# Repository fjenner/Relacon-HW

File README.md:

# Relacon Relay Controller

## Overview

The Relacon relay controller is intended to be an open source hardware alternative to the [ADU218](https://www.ontrak.net/ADU218.htm) USB relay I/O interface from [OnTrak Control Systems, Inc](https://www.ontrak.net). The Relacon is not as robust as the commercial offering, but what it lacks in polish it makes up for in cost. Relacon relay controller is about an order of magnitude cheaper to make yourself compared to purchasing an ADU218.

## License

This hardware is Open Source Hardware licensed under the [Creative Commons Attribution 4.0 International (CC BY 4.0)](https://creativecommons.org/licenses/by/4.0/)  license.

## Features

The Relacon has numerous features that make it attractive for low cost applications:

* 8 solid-state relays capable of switching loads up to 60V AC/DC at 1A
* LED indicators corresponding to each relay output
* 8 digital inputs featuring event counters and configurable debounce setting
* Configurable watchdog to fail-open the relays if not actively receiving data from the host
* Full-speed USB Human Interface Device (HID) interface to PC requiring no custom drivers
* Compatibile with existing ADU218-based software applications
* Open source hardware design
    * Easy to modify to substitute in higher-power relays, etc.
* Open source firmware
    * Potential to utilize additional microcontroller peripherals (or repurpose digital inputs) on the expansion header
* No programmer hardware necessary to load the firmware (uses USB DFU bootloader)

That said, the current version of the Relacon hardware (rev. 1) lacks several of the niceties offered by the commercial ADU218 hardware, as indicated in the table below.

Feature | ADU218 | Relacon
--------|--------|---------
120V load capability | :heavy_check_mark: | :x:<br/>(60V load rating)
24V tolerant inputs | :heavy_check_mark: | :x:<br/>(3.3V inputs)
Operational status LED indicator | :heavy_check_mark: | :x:
Certified to various electrical standards | :heavy_check_mark: | :x:
Sturdy enclosure | :heavy_check_mark: | :x:

### Feature/Pin Mapping

The Relacon hardware follows the protocol and conventions of the OnTrak ADU218 relay controller. Because of hardware differences between the two devices, the port/pin designations used in the protocol layer do not directly map to those of the STM32F042K6. The mappings are shown below:

ADU Protocol Pin/Feature | STM32F042K6 Pin Mapping
-------------------|------------------------------
Relay PORTK[0] | PA0
Relay PORTK[1] | PA1
Relay PORTK[2] | PA2
Relay PORTK[3] | PA3
Relay PORTK[4] | PA4
Relay PORTK[5] | PA5
Relay PORTK[6] | PA6
Relay PORTK[7] | PA7
Digital Input PORTA[0] / Event Counter 0 | PB0
Digital Input PORTA[1] / Event Counter 1 | PB1
Digital Input PORTA[2] / Event Counter 2 | PA8 (note that there is no PB2 pin on the STM32F042K6T6 device)
Digital Input PORTA[3] / Event Counter 3 | PB3
Digital Input PORTB[0] / Event Counter 4 | PB4
Digital Input PORTB[1] / Event Counter 5 | PB5
Digital Input PORTB[2] / Event Counter 6 | PB6
Digital Input PORTB[3] / Event Counter 7 | PB7

Note that the silkscreen labels on the board near the terminal block shows the "K" designation for the relays. The silkscreen on the expansion header shows the actual STM32F042K6 pin names.

## Design

### Design Tools

This hardware was designed using the [KiCad](https://kicad.org/) electronic design automation suite for schematic capture and PCB layout. Additional scripts were used for generating the BOM for assembly [per instructions at JLCPCB](https://support.jlcpcb.com/article/84-how-to-generate-the-bom-and-centroid-file-from-kicad).

### Hardware Design

One of the design goals for this board was to support USB bootloading of the firmware on an unprogrammed microcontroller, allowing anyone to build and program the board without requiring any additional programming hardware. This contrained the selection of microcontrollers quite a bit. Another constraining factor was that I intended from the start to use JLCPCB for the PCB fabrication and assembly, so I was limited to their selection of microcontrollers. I ultimately settled on using a STM32F042K6T6 microcontroller.

Is a 32-bit ARM Cortex-M0 overkill for a simple relay controller? Absolutely. However, it was surprisingly inexpensive (I originally got them for $1.28 in individual quantities, although I may have capitalized on a price mistake, as they're now listed at $3.69 at the time of this writing), has an open source basic peripheral library, is compatible with the open source TinyUSB stack, and allows for the use of the well-known ARM GCC toolchain for firmware development.

The circuit design for this hardware is very straightforward. Power and communication with the PC come from the USB connection. A linear voltage regulator and some filtering capacitors are used to drop the voltage from the 5V USB VBUS power to the 3.3V suitable for the microcontroller. The microcontroller contains the firmware that controls the overall behavior of the product.

Although the STM32F042K6 GPIO pins are capable of sourcing or sinking up to 25mA each, the datasheet specifies that there is a cumulative limit of 80mA sourced or sunk among all GPIO pins. This means that when all 8 relays are enabled, those pins must not source/sink more than 10mA each. While 10mA should be sufficient to drive both the indicator LED and the solid-state relay for that channel, it is only by a narrow margin. In order to get more headroom (which may be useful particularly if additional GPIO are being used on the expansion header), a ULN2803A Darlington transistor array is used to drive the indicator LED and relay. The ULN2803A only draws about 1mA per channel, but can drive up to 500mA per channel. While overkill for the base design, this additional drive strength may be useful for modifications that substitute in traditional electromechanical relays, which typically require much more drive current than solid state relays but also provide higher power load switching.

An expansion header exposing additional pins from the microcontroller has been added for two purposes:
* This exposes the 8 input pins required for maintaining functional equivalence with the ADU218
* This makes additional microcontroller pins available for auxiliary functions through modifications to the open source [firmware](https://github.com/fjenner/Relacon-FW).

## Production

These boards (in particular, the component selection) were designed with [JLCPCB](https://jlcpcb.com/) in mind for low cost manufacturing and assembly. The Gerber files for the relevant layers, as well as the drill files, are located in the [gerber](production/gerber) directory, and have been generated per the instructions from JLCPCB [here](https://support.jlcpcb.com/article/102-kicad-515---generating-gerber-and-drill-files).

The BOM used for the assembly, as well as the pick-and-place files, are located in the [assembly](production/assembly) directory. These files have been prepared as described by [JLCPCB](https://support.jlcpcb.com/article/84-how-to-generate-the-bom-and-centroid-file-from-kicad). JLCPCB has a preview tool that shows the component placement and orientation given the pick-and-place files, and notes that the rotation/orientation [may need to be compensated for](https://support.jlcpcb.com/article/99-does-the-red-dot-means-pin-1-in-the-placement-previewer) if there are discrepancies between the zero-degree orientation of the footprint in the KiCad component library vs. their pick-and-place data for the component. This was the case for the U1, U2, and U3 components, so their rotation was manually adjusted in the pick-and-place files after the initial generation.

### Cost

At the time that I placed my order, the total cost (including shipping) for having JLCPCB fab and assemble 5 boards was $77.67, which comes out to about $15.54 per board. However, this includes a $7 discount from a new user coupon code, and that I believe there may have been a price mistake on the STM32F042K6, so take this cost figure with a grain of salt.

Importantly, JLCPCB does not do any through-hole assembly, so the price above does not include the cost of the through-hole parts: the USB connector, terminal blocks, and pin header. Fortunately, these are relatively low cost components. As of the time of this writing, the total cost to purchase those additional through-hole components for the 5 boards would come out to $8.18 (not including shipping), bringing the cost per board up to $17.18.

## Known Issues

Known issues are tracked in the GitHub issue tracker. However, critical issues affecting fundamental operation of the device are described here.

### BOOT0 Pin is Floating

In the current version of the hardware (Relacon Rev 1), the STM32F042K6 `BOOT0` pin (a.k.a `PB8`) is floating. This means that when the device is connected to USB and powers up, it is indeterminate as to whether it will enter the DFU bootloader or the normal firmware application. While an unfortunate oversight, there are several very easy workarounds for this as described below.

#### Workaround 1: Use a jumper on the expansion header to select the desired boot mode
Using a jumper wire, connect the `PB8` pin on the expansion header to either of the `GND` pins for normal firmware boot, or to the `+3V3` pin for DFU bootloading. Fortunately, because the `PB8` pin is adjacent to a `GND` pin on the header, a standard 2-pin jumper block can be used to pull down the `PB8` pin for normal firmware operation.

#### Workaround 2: Solder a pulldown resistor to the underside of the pin header
A small surface-mount resistor (in the 10k~100k range) can be easily added to the underside of the board, fitting quite nicely between the `PB8` pin and the and the adjacent `GND` pin on the expansion header. This approach is functionally similar to the above except that the expansion header pins are physically freed up during normal operation. You will still need to use a wire to temporarily jump the `PB8` pin to `+3V3` when flashing the firmware with the DFU bootloader.

#### Workaround 3: Disable DFU in the STM32F042K6 option byte after programming
This approach hasn't been tested, but in theory, programming the `BOOT_SEL` bit to 0 and the `nBOOT0` bit to 1 in the STM32F042K6 "option byte" should disable selection of the boot mode through the `BOOT0` pin and cause the device to only boot the user firmware application. This has the disadvantage that it will not be possible to update the firmware (or change the option byte to re-enable the `BOOT0` selection) without additional programming hardware.

## Firmware

For more information about the firmware that runs on the Relacon board, including how to fetch, build, and flash it, see the [Relacon Firmware repository](https://github.com/fjenner/Relacon-FW).

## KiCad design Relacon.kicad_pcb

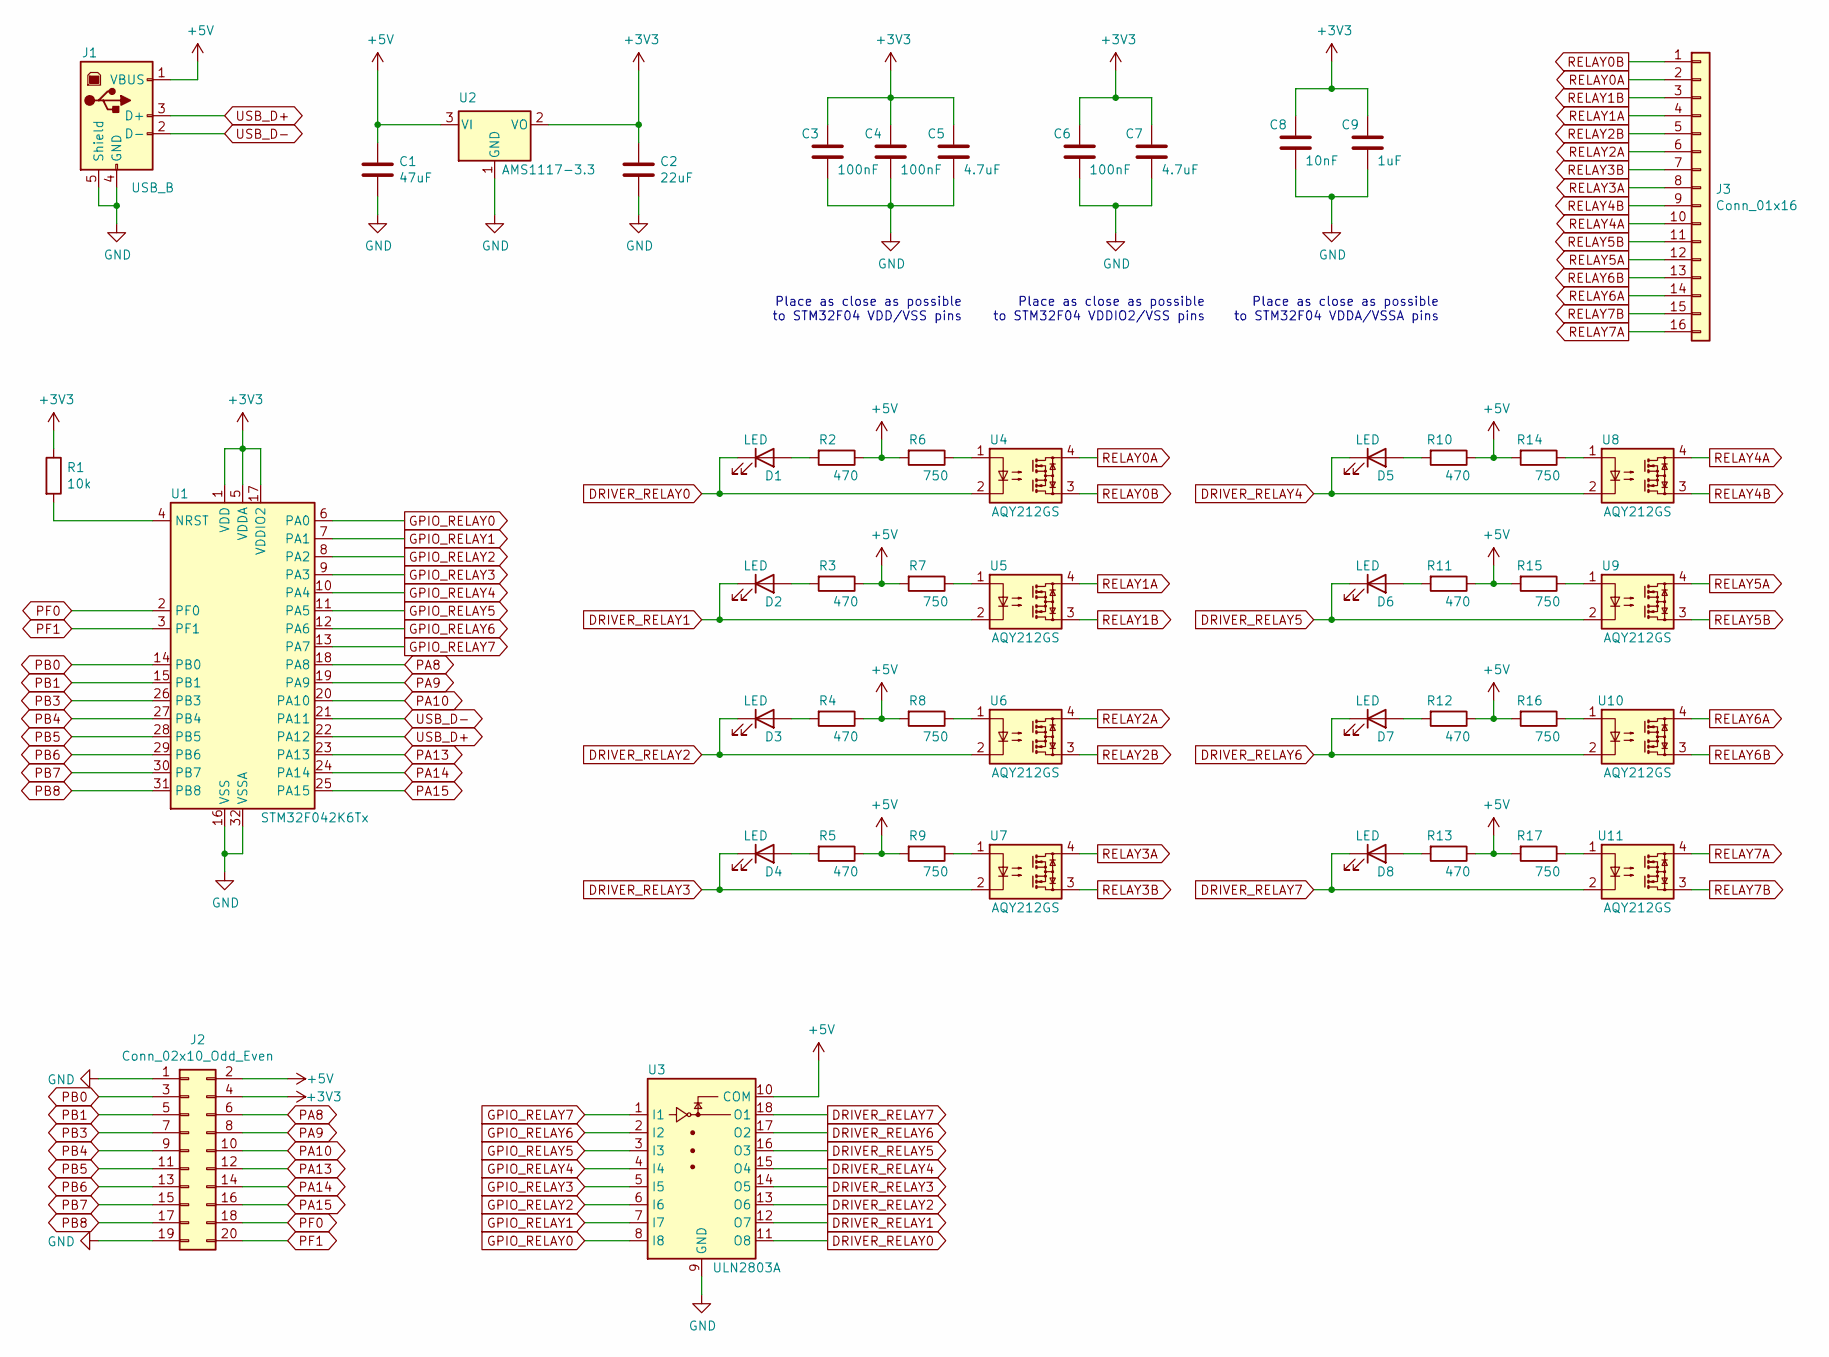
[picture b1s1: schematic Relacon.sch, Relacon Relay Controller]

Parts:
C1: 47uF; C_1206_3216Metric; LCSC C96123
C2: 22uF; C_0805_2012Metric; LCSC C45783
C3, C4, C6: 100nF; C_0402_1005Metric; LCSC C1525
C5, C7: 4.7uF; C_0402_1005Metric; LCSC C23733
C8: 10nF; C_0402_1005Metric; LCSC C15195
C9: 1uF; C_0402_1005Metric; LCSC C52923
D1, D2, D3, D4, D5, D6, D7, D8: LED; LED_0603_1608Metric; LCSC C72041
J1: USB_B; USB_B_Lumberg_2411_02_Horizontal
J2: Conn_02x10_Odd_Even; PinHeader_2x10_P2.54mm_Vertical
J3: Conn_01x16; TerminalBlock_Phoenix_MKDS-1,5-16_1x16_P5.00mm_Horizontal
R1: 10k; R_0805_2012Metric; LCSC C17414
R2, R3, R4, R5, R10, R11, R12, R13: 470; R_0805_2012Metric; LCSC C17710
R6, R7, R8, R9, R14, R15, R16, R17: 750; R_0805_2012Metric; LCSC C17818
U1: STM32F042K6Tx; LQFP-32_7x7mm_P0.8mm; LCSC C69216
U2: AMS1117-3.3; SOT-223-3_TabPin2; LCSC C6186
U3: ULN2803A; SOIC-18W_7.5x11.6mm_P1.27mm; LCSC C9683
U4, U5, U6, U7, U8, U9, U10, U11: AQY212GS; SO-4_4.4x4.3mm_P2.54mm; LCSC C129283

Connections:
+3V3: C2.1, C3.1, C4.1, C5.1, C6.1, C7.1, C8.1, C9.1, J2.4, R1.1, U1.1 (VDD), U1.5 (VDDA), U1.17 (VDDIO2), U2.2 (VO)
+5V: C1.1, J1.1 (VBUS), J2.2, R2.1, R3.1, R4.1, R5.1, R6.2, R7.2, R8.2, R9.2, R10.1, R11.1, R12.1, R13.1, R14.2, R15.2, R16.2, R17.2, U2.3 (VI), U3.10 (COM)
DRIVER_RELAY0: D1.1 (K), U3.11 (O8), U4.2
DRIVER_RELAY1: D2.1 (K), U3.12 (O7), U5.2
DRIVER_RELAY2: D3.1 (K), U3.13 (O6), U6.2
DRIVER_RELAY3: D4.1 (K), U3.14 (O5), U7.2
DRIVER_RELAY4: D5.1 (K), U3.15 (O4), U8.2
DRIVER_RELAY5: D6.1 (K), U3.16 (O3), U9.2
DRIVER_RELAY6: D7.1 (K), U3.17 (O2), U10.2
DRIVER_RELAY7: D8.1 (K), U3.18 (O1), U11.2
GND: C1.2, C2.2, C3.2, C4.2, C5.2, C6.2, C7.2, C8.2, C9.2, J1.4 (GND), J1.5 (Shield), J2.1, J2.19, U1.16 (VSS), U1.32 (VSSA), U2.1 (GND), U3.9 (GND)
GPIO_RELAY0: U1.6 (PA0), U3.8 (I8)
GPIO_RELAY1: U1.7 (PA1), U3.7 (I7)
GPIO_RELAY2: U1.8 (PA2), U3.6 (I6)
GPIO_RELAY3: U1.9 (PA3), U3.5 (I5)
GPIO_RELAY4: U1.10 (PA4), U3.4 (I4)
GPIO_RELAY5: U1.11 (PA5), U3.3 (I3)
GPIO_RELAY6: U1.12 (PA6), U3.2 (I2)
GPIO_RELAY7: U1.13 (PA7), U3.1 (I1)
unnamed: D1.2 (A), R2.2
unnamed: D2.2 (A), R3.2
unnamed: D3.2 (A), R4.2
unnamed: D4.2 (A), R5.2
unnamed: D5.2 (A), R10.2
unnamed: D6.2 (A), R11.2
unnamed: D7.2 (A), R12.2
unnamed: D8.2 (A), R13.2
unnamed: R1.2, U1.4 (NRST)
unnamed: R6.1, U4.1
unnamed: R7.1, U5.1
unnamed: R8.1, U6.1
unnamed: R9.1, U7.1
unnamed: R14.1, U8.1
unnamed: R15.1, U9.1
unnamed: R16.1, U10.1
unnamed: R17.1, U11.1
PA8: J2.6, U1.18 (PA8)
PA9: J2.8, U1.19 (PA9)
PA10: J2.10, U1.20 (PA10)
PA13: J2.12, U1.23 (PA13)
PA14: J2.14, U1.24 (PA14)
PA15: J2.16, U1.25 (PA15)
PB0: J2.3, U1.14 (PB0)
PB1: J2.5, U1.15 (PB1)
PB3: J2.7, U1.26 (PB3)
PB4: J2.9, U1.27 (PB4)
PB5: J2.11, U1.28 (PB5)
PB6: J2.13, U1.29 (PB6)
PB7: J2.15, U1.30 (PB7)
PB8: J2.17, U1.31 (PB8)
PF0: J2.18, U1.2 (PF0)
PF1: J2.20, U1.3 (PF1)
RELAY0A: J3.2, U4.4
RELAY0B: J3.1, U4.3
RELAY1A: J3.4, U5.4
RELAY1B: J3.3, U5.3
RELAY2A: J3.6, U6.4
RELAY2B: J3.5, U6.3
RELAY3A: J3.8, U7.4
RELAY3B: J3.7, U7.3
RELAY4A: J3.10, U8.4
RELAY4B: J3.9, U8.3
RELAY5A: J3.12, U9.4
RELAY5B: J3.11, U9.3
RELAY6A: J3.14, U10.4
RELAY6B: J3.13, U10.3
RELAY7A: J3.16, U11.4
RELAY7B: J3.15, U11.3
USB_D+: J1.3 (D+), U1.22 (PA12)
USB_D-: J1.2 (D-), U1.21 (PA11)

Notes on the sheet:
Place as close as possible to STM32F04 VDD/VSS pins
Place as close as possible to STM32F04 VDDIO2/VSS pins
Place as close as possible to STM32F04 VDDA/VSSA pins

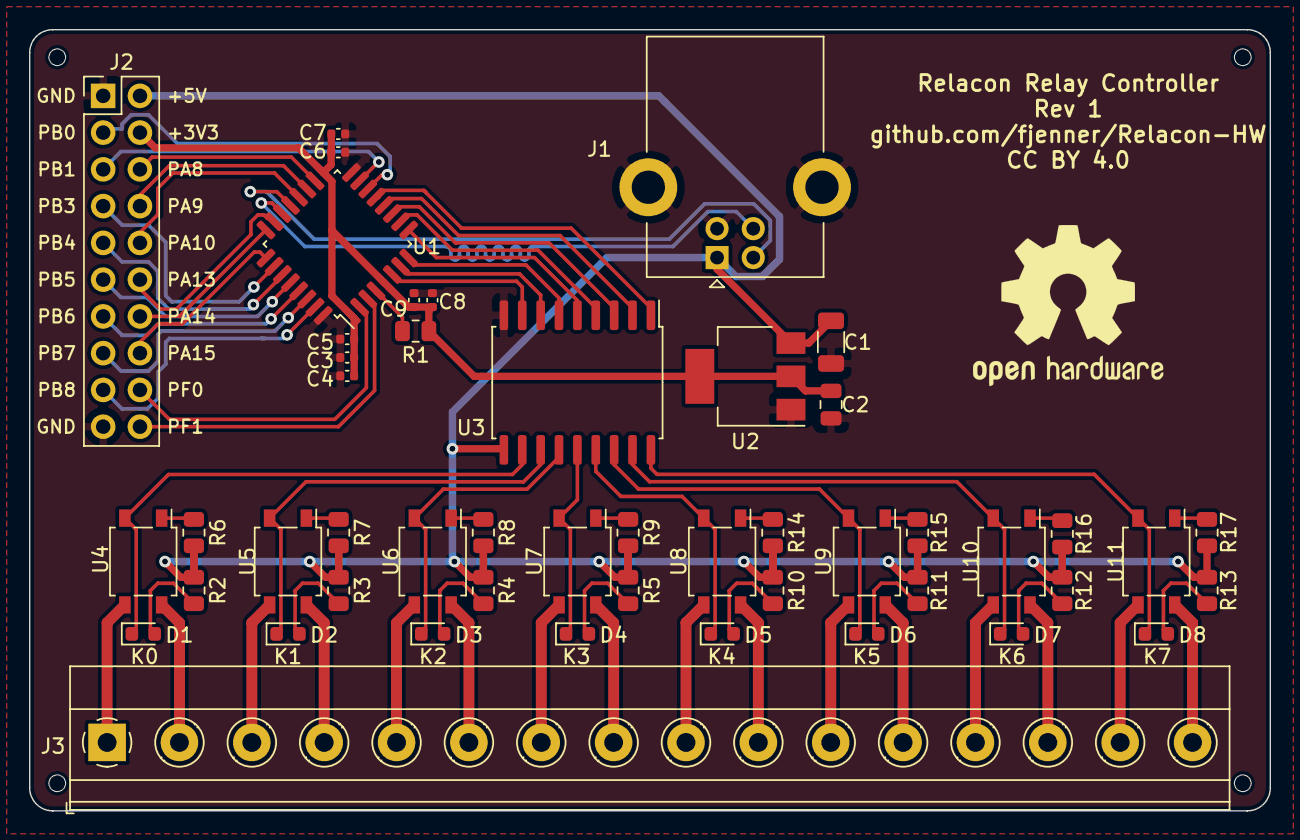
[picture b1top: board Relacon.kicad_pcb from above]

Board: 2 copper layers, 85.7 x 54.0 mm, 48 parts (0 on the bottom side), 70 nets.

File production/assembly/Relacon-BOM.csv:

Comment,Designator,Footprint,LCSC
"47uF","C1","Capacitor_SMD:C_1206_3216Metric","C96123"
"22uF","C2","Capacitor_SMD:C_0805_2012Metric","C45783"
"100nF","C3,C4,C6","Capacitor_SMD:C_0402_1005Metric","C1525"
"4.7uF","C5,C7","Capacitor_SMD:C_0402_1005Metric","C23733"
"10nF","C8","Capacitor_SMD:C_0402_1005Metric","C15195"
"1uF","C9","Capacitor_SMD:C_0402_1005Metric","C52923"
"LED","D1,D2,D3,D4,D5,D6,D7,D8","LED_SMD:LED_0603_1608Metric","C72041"
"USB_B","J1","Connector_USB:USB_B_Lumberg_2411_02_Horizontal",""
"Conn_02x10_Odd_Even","J2","Connector_PinHeader_2.54mm:PinHeader_2x10_P2.54mm_Vertical",""
"Conn_01x16","J3","TerminalBlock_Phoenix:TerminalBlock_Phoenix_MKDS-1,5-16_1x16_P5.00mm_Horizontal",""
"10k","R1","Resistor_SMD:R_0805_2012Metric","C17414"
"470","R2,R3,R4,R5,R10,R11,R12,R13","Resistor_SMD:R_0805_2012Metric","C17710"
"750","R6,R7,R8,R9,R14,R15,R16,R17","Resistor_SMD:R_0805_2012Metric","C17818"
"STM32F042K6Tx","U1","Package_QFP:LQFP-32_7x7mm_P0.8mm","C69216"
"AMS1117-3.3","U2","Package_TO_SOT_SMD:SOT-223-3_TabPin2","C6186"
"ULN2803A","U3","Package_SO:SOIC-18W_7.5x11.6mm_P1.27mm","C9683"
"AQY212GS","U4,U5,U6,U7,U8,U9,U10,U11","Package_SO:SO-4_4.4x4.3mm_P2.54mm","C129283"

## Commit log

2021-01-10 Added device illustration to README
2021-01-10 Updated URL on silk screen

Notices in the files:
Relacon.kicad_pcb:
License: CC BY 4.0
